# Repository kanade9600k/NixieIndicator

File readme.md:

# NixieIndicator

## 概要

* ニキシー管を制御するための基板
* 最大12管まで制御可能

## 回路図

## 外観

* 表

* 裏

## その他

* 高電圧注意
* 一応手元で動きましたが，動作保証はできません

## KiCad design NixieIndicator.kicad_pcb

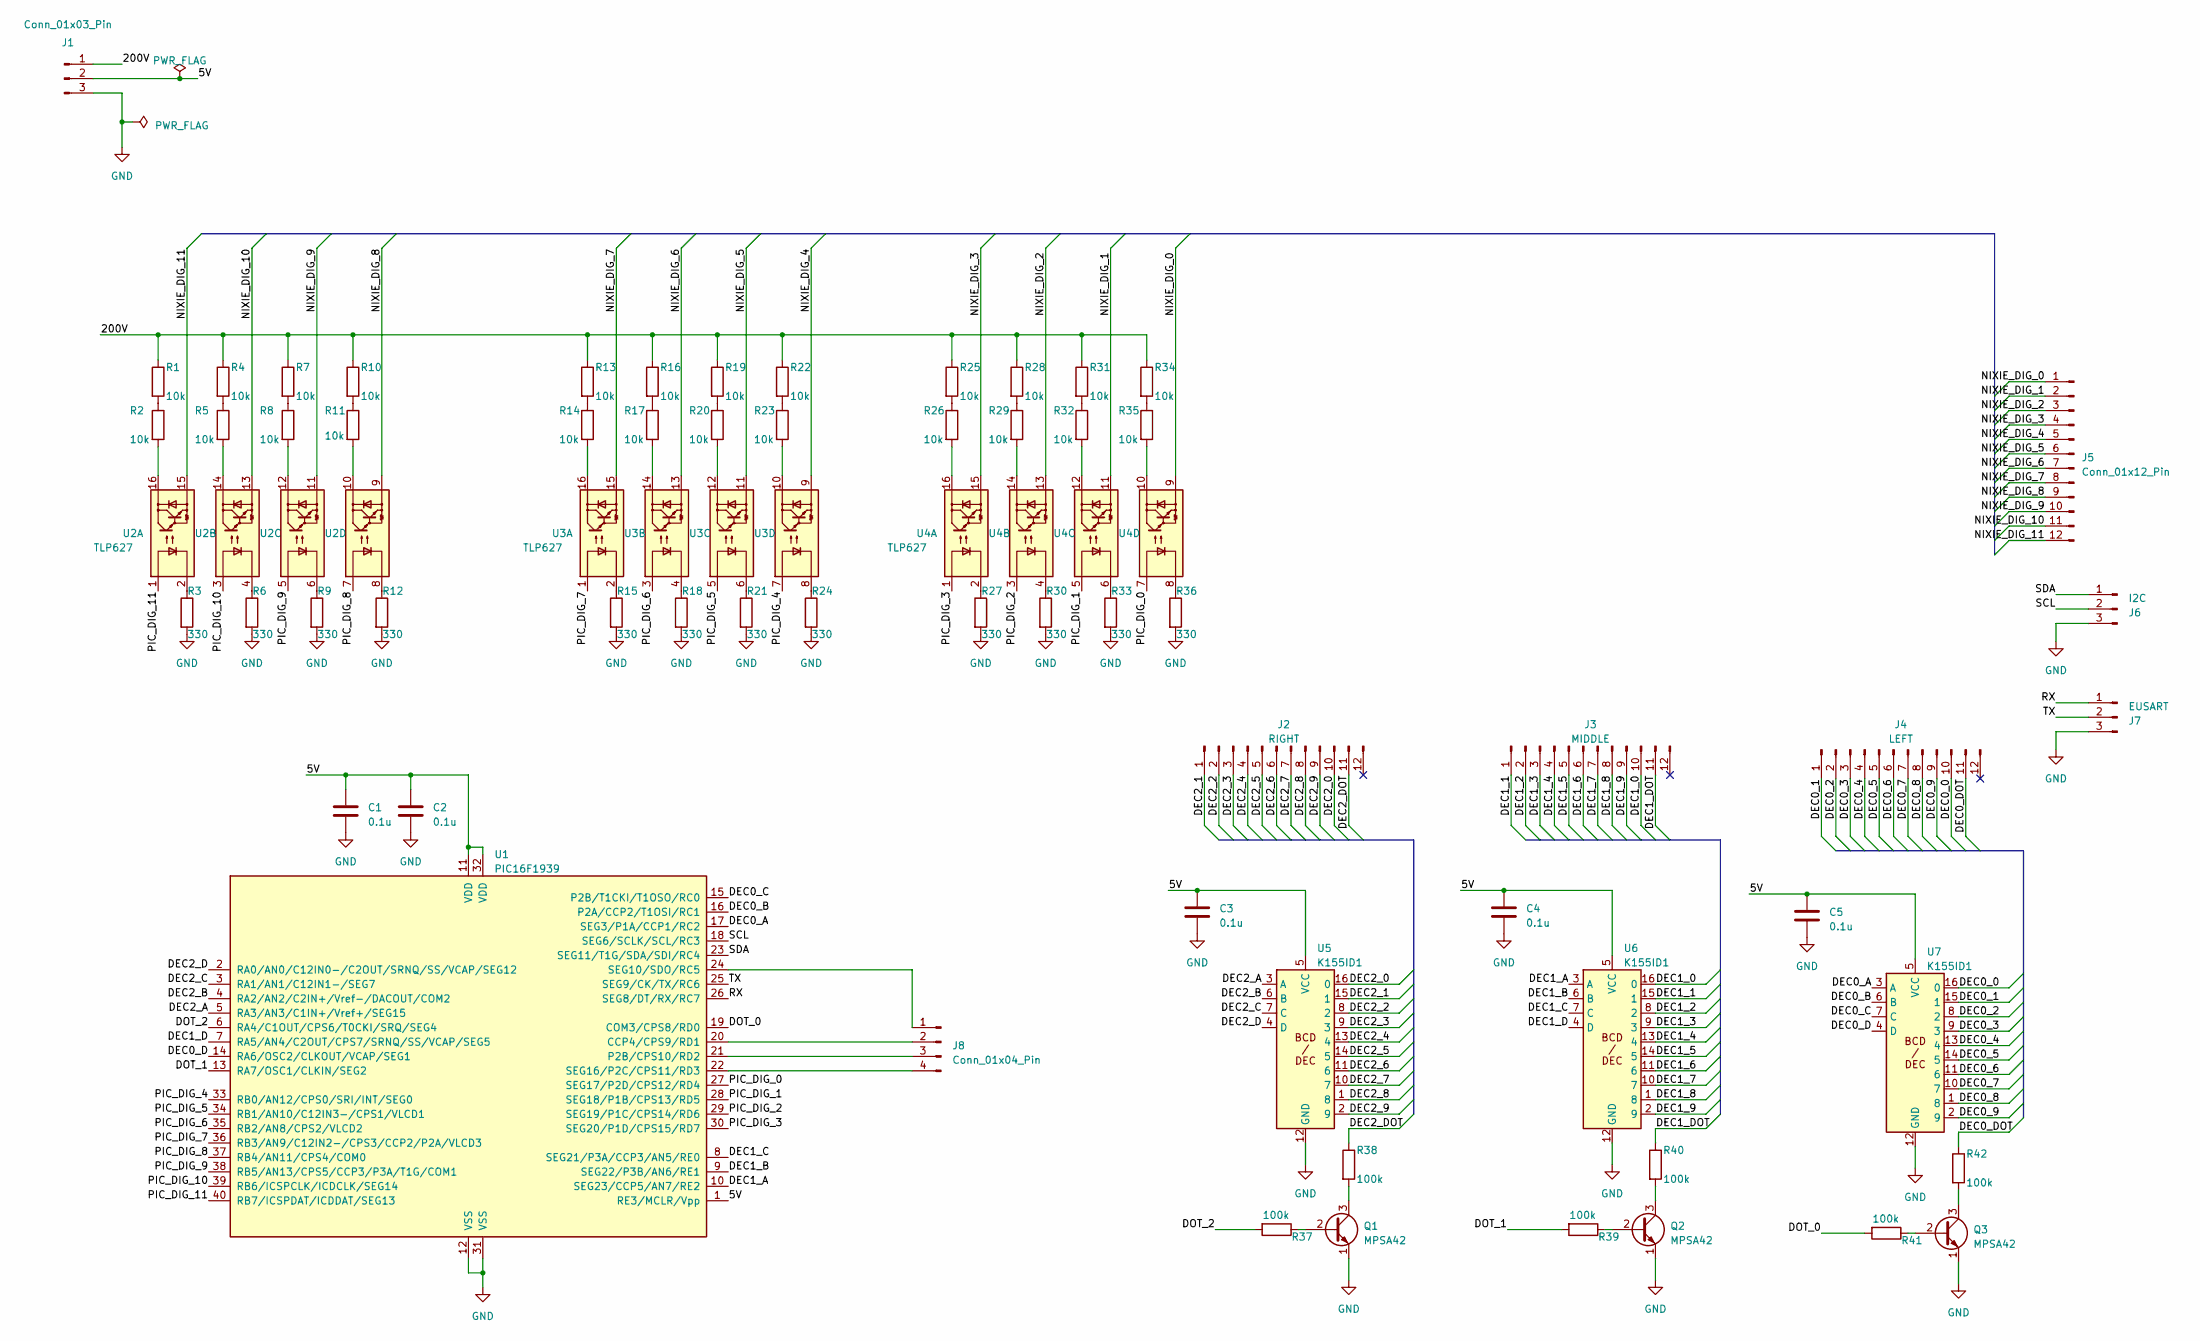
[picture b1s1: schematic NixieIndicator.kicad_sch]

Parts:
C1, C2, C3, C4, C5: 0.1u; C_Disc_D3.0mm_W2.0mm_P2.50mm
J1: Conn_01x03_Pin; JST_XH_B3B-XH-A_1x03_P2.50mm_Vertical
J2: RIGHT; JST_XH_S12B-XH-A_1x12_P2.50mm_Horizontal
J3: MIDDLE; JST_XH_S12B-XH-A_1x12_P2.50mm_Horizontal
J4: LEFT; JST_XH_S12B-XH-A_1x12_P2.50mm_Horizontal
J5: Conn_01x12_Pin; JST_XH_S12B-XH-A_1x12_P2.50mm_Horizontal
J6: I2C; JST_XH_B3B-XH-A_1x03_P2.50mm_Vertical
J7: EUSART; JST_XH_B3B-XH-A_1x03_P2.50mm_Vertical
J8: Conn_01x04_Pin; PinHeader_1x04_P2.54mm_Vertical
Q1, Q2, Q3: MPSA42; TO-92_Inline
R1, R2, R4, R5, R7, R8, R10, R11, R13, R14, R16, R17, R19, R20, R22, R23, R25, R26, R28, R29, R31, R32, R34, R35: 10k; R_Axial_DIN0207_L6.3mm_D2.5mm_P10.16mm_Horizontal
R3, R6, R9, R12, R15, R18, R21, R24, R27, R30, R33, R36: 330; R_Axial_DIN0207_L6.3mm_D2.5mm_P10.16mm_Horizontal
R37, R38, R39, R40, R41, R42: 100k; R_Axial_DIN0207_L6.3mm_D2.5mm_P10.16mm_Horizontal
U1: PIC16F1939; DIP-40_W15.24mm_Socket
U2, U3, U4: TLP627; DIP-16_W7.62mm_Socket
U5, U6, U7: K155ID1; DIP-16_W7.62mm_Socket

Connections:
/5V: C1.1, C2.1, C3.1, C4.1, C5.1, J1.2, U1.1 (RE3/MCLR/Vpp), U1.11 (VDD), U1.32 (VDD), U5.5 (VCC), U6.5 (VCC), U7.5 (VCC)
/200V: J1.1, R1.1, R4.1, R7.1, R10.1, R13.1, R16.1, R19.1, R22.1, R25.1, R28.1, R31.1, R34.1
/DEC0_0: J4.10, U7.16 (0)
/DEC0_1: J4.1, U7.15 (1)
/DEC0_2: J4.2, U7.8 (2)
/DEC0_3: J4.3, U7.9 (3)
/DEC0_4: J4.4, U7.13 (4)
/DEC0_5: J4.5, U7.14 (5)
/DEC0_6: J4.6, U7.11 (6)
/DEC0_7: J4.7, U7.10 (7)
/DEC0_8: J4.8, U7.1 (8)
/DEC0_9: J4.9, U7.2 (9)
/DEC0_A: U1.17 (SEG3/P1A/CCP1/RC2), U7.3 (A)
/DEC0_B: U1.16 (P2A/CCP2/T1OSI/RC1), U7.6 (B)
/DEC0_C: U1.15 (P2B/T1CKI/T1OSO/RC0), U7.7 (C)
/DEC0_D: U1.14 (RA6/OSC2/CLKOUT/VCAP/SEG1), U7.4 (D)
/DEC0_DOT: J4.11, R42.1
/DEC1_0: J3.10, U6.16 (0)
/DEC1_1: J3.1, U6.15 (1)
/DEC1_2: J3.2, U6.8 (2)
/DEC1_3: J3.3, U6.9 (3)
/DEC1_4: J3.4, U6.13 (4)
/DEC1_5: J3.5, U6.14 (5)
/DEC1_6: J3.6, U6.11 (6)
/DEC1_7: J3.7, U6.10 (7)
/DEC1_8: J3.8, U6.1 (8)
/DEC1_9: J3.9, U6.2 (9)
/DEC1_A: U1.10 (SEG23/CCP5/AN7/RE2), U6.3 (A)
/DEC1_B: U1.9 (SEG22/P3B/AN6/RE1), U6.6 (B)
/DEC1_C: U1.8 (SEG21/P3A/CCP3/AN5/RE0), U6.7 (C)
/DEC1_D: U1.7 (RA5/AN4/C2OUT/CPS7/SRNQ/SS/VCAP/SEG5), U6.4 (D)
/DEC1_DOT: J3.11, R40.1
/DEC2_0: J2.10, U5.16 (0)
/DEC2_1: J2.1, U5.15 (1)
/DEC2_2: J2.2, U5.8 (2)
/DEC2_3: J2.3, U5.9 (3)
/DEC2_4: J2.4, U5.13 (4)
/DEC2_5: J2.5, U5.14 (5)
/DEC2_6: J2.6, U5.11 (6)
/DEC2_7: J2.7, U5.10 (7)
/DEC2_8: J2.8, U5.1 (8)
/DEC2_9: J2.9, U5.2 (9)
/DEC2_A: U1.5 (RA3/AN3/C1IN+/Vref+/SEG15), U5.3 (A)
/DEC2_B: U1.4 (RA2/AN2/C2IN+/Vref-/DACOUT/COM2), U5.6 (B)
/DEC2_C: U1.3 (RA1/AN1/C12IN1-/SEG7), U5.7 (C)
/DEC2_D: U1.2 (RA0/AN0/C12IN0-/C2OUT/SRNQ/SS/VCAP/SEG12), U5.4 (D)
/DEC2_DOT: J2.11, R38.1
/DOT_0: R41.2, U1.19 (COM3/CPS8/RD0)
/DOT_1: R39.2, U1.13 (RA7/OSC1/CLKIN/SEG2)
/DOT_2: R37.2, U1.6 (RA4/C1OUT/CPS6/T0CKI/SRQ/SEG4)
/NIXIE_DIG_0: J5.1, U4.9
/NIXIE_DIG_1: J5.2, U4.11
/NIXIE_DIG_2: J5.3, U4.13
/NIXIE_DIG_3: J5.4, U4.15
/NIXIE_DIG_4: J5.5, U3.9
/NIXIE_DIG_5: J5.6, U3.11
/NIXIE_DIG_6: J5.7, U3.13
/NIXIE_DIG_7: J5.8, U3.15
/NIXIE_DIG_8: J5.9, U2.9
/NIXIE_DIG_9: J5.10, U2.11
/NIXIE_DIG_10: J5.11, U2.13
/NIXIE_DIG_11: J5.12, U2.15
/PIC_DIG_0: U1.27 (SEG17/P2D/CPS12/RD4), U4.7
/PIC_DIG_1: U1.28 (SEG18/P1B/CPS13/RD5), U4.5
/PIC_DIG_2: U1.29 (SEG19/P1C/CPS14/RD6), U4.3
/PIC_DIG_3: U1.30 (SEG20/P1D/CPS15/RD7), U4.1
/PIC_DIG_4: U1.33 (RB0/AN12/CPS0/SRI/INT/SEG0), U3.7
/PIC_DIG_5: U1.34 (RB1/AN10/C12IN3-/CPS1/VLCD1), U3.5
/PIC_DIG_6: U1.35 (RB2/AN8/CPS2/VLCD2), U3.3
/PIC_DIG_7: U1.36 (RB3/AN9/C12IN2-/CPS3/CCP2/P2A/VLCD3), U3.1
/PIC_DIG_8: U1.37 (RB4/AN11/CPS4/COM0), U2.7
/PIC_DIG_9: U1.38 (RB5/AN13/CPS5/CCP3/P3A/T1G/COM1), U2.5
/PIC_DIG_10: U1.39 (RB6/ICSPCLK/ICDCLK/SEG14), U2.3
/PIC_DIG_11: U1.40 (RB7/ICSPDAT/ICDDAT/SEG13), U2.1
/RX: J7.1, U1.26 (SEG8/DT/RX/RC7)
/SCL: J6.2, U1.18 (SEG6/SCLK/SCL/RC3)
/SDA: J6.1, U1.23 (SEG11/T1G/SDA/SDI/RC4)
/TX: J7.2, U1.25 (SEG9/CK/TX/RC6)
GND: C1.2, C2.2, C3.2, C4.2, C5.2, J1.3, J6.3, J7.3, Q1.1 (E), Q2.1 (E), Q3.1 (E), R3.2, R6.2, R9.2, R12.2, R15.2, R18.2, R21.2, R24.2, R27.2, R30.2, R33.2, R36.2, U1.12 (VSS), U1.31 (VSS), U5.12 (GND), U6.12 (GND), U7.12 (GND)
unnamed: J8.1, U1.24 (SEG10/SDO/RC5)
unnamed: J8.2, U1.20 (CCP4/CPS9/RD1)
unnamed: J8.3, U1.21 (P2B/CPS10/RD2)
unnamed: J8.4, U1.22 (SEG16/P2C/CPS11/RD3)
unnamed: Q1.2 (B), R37.1
unnamed: Q1.3 (C), R38.2
unnamed: Q2.2 (B), R39.1
unnamed: Q2.3 (C), R40.2
unnamed: Q3.2 (B), R41.1
unnamed: Q3.3 (C), R42.2
unnamed: R1.2, R2.1
unnamed: R2.2, U2.16
unnamed: R3.1, U2.2
unnamed: R4.2, R5.1
unnamed: R5.2, U2.14
unnamed: R6.1, U2.4
unnamed: R7.2, R8.1
unnamed: R8.2, U2.12
unnamed: R9.1, U2.6
unnamed: R10.2, R11.1
unnamed: R11.2, U2.10
unnamed: R12.1, U2.8
unnamed: R13.2, R14.1
unnamed: R14.2, U3.16
unnamed: R15.1, U3.2
unnamed: R16.2, R17.1
unnamed: R17.2, U3.14
unnamed: R18.1, U3.4
unnamed: R19.2, R20.1
unnamed: R20.2, U3.12
unnamed: R21.1, U3.6
unnamed: R22.2, R23.1
unnamed: R23.2, U3.10
unnamed: R24.1, U3.8
unnamed: R25.2, R26.1
unnamed: R26.2, U4.16
unnamed: R27.1, U4.2
unnamed: R28.2, R29.1
unnamed: R29.2, U4.14
unnamed: R30.1, U4.4
unnamed: R31.2, R32.1
unnamed: R32.2, U4.12
unnamed: R33.1, U4.6
unnamed: R34.2, R35.1
unnamed: R35.2, U4.10
unnamed: R36.1, U4.8

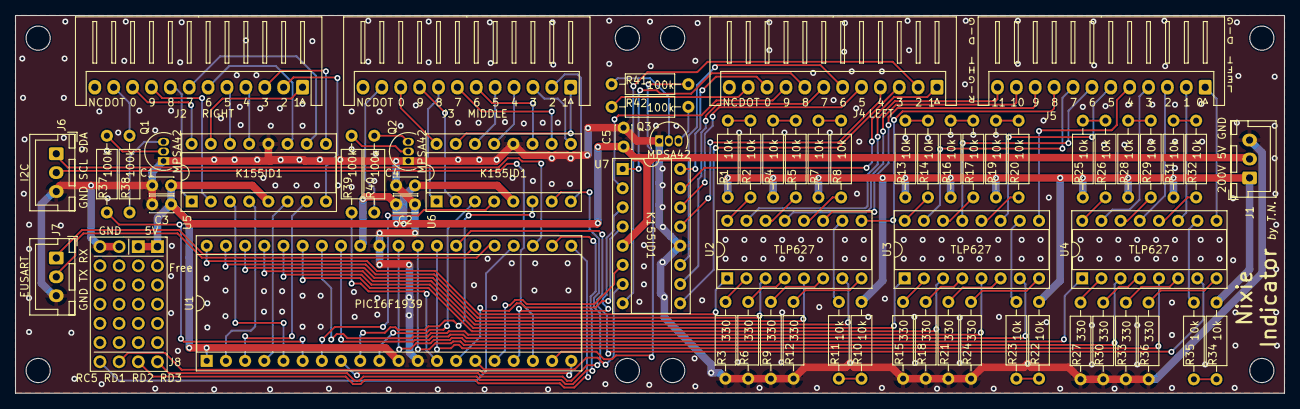
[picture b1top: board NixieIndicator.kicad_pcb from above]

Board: 2 copper layers, 168.0 x 50.0 mm, 65 parts (0 on the bottom side), 125 nets.

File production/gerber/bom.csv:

Designator,Footprint,Quantity,Value,LCSC Part #
"C1, C2, C3, C4, C5",C_Disc_D3.0mm_W2.0mm_P2.50mm,5,0.1u,
J1,JST_XH_B3B-XH-A_1x03_P2.50mm_Vertical,1,Conn_01x03_Pin,
J2,JST_XH_S12B-XH-A_1x12_P2.50mm_Horizontal,1,RIGHT,
J3,JST_XH_S12B-XH-A_1x12_P2.50mm_Horizontal,1,MIDDLE,
J4,JST_XH_S12B-XH-A_1x12_P2.50mm_Horizontal,1,LEFT,
J5,JST_XH_S12B-XH-A_1x12_P2.50mm_Horizontal,1,Conn_01x12_Pin,
J6,JST_XH_B3B-XH-A_1x03_P2.50mm_Vertical,1,I2C,
J7,JST_XH_B3B-XH-A_1x03_P2.50mm_Vertical,1,EUSART,
J8,PinHeader_1x04_P2.54mm_Vertical,1,Conn_01x04_Pin,
"Q1, Q2, Q3",TO-92_Inline,3,MPSA42,
"R1, R10, R11, R13, R14, R16, R17, R19, R2, R20, R22, R23, R25, R26, R28, R29, R31, R32, R34, R35, R4, R5, R7, R8",R_Axial_DIN0207_L6.3mm_D2.5mm_P10.16mm_Horizontal,24,10k,
"R12, R15, R18, R21, R24, R27, R3, R30, R33, R36, R6, R9",R_Axial_DIN0207_L6.3mm_D2.5mm_P10.16mm_Horizontal,12,330,
"R37, R38, R39, R40, R41, R42",R_Axial_DIN0207_L6.3mm_D2.5mm_P10.16mm_Horizontal,6,100k,
U1,DIP-40_W15.24mm_Socket,1,PIC16F1939,
"U2, U3, U4",DIP-16_W7.62mm_Socket,3,TLP627,
"U5, U6, U7",DIP-16_W7.62mm_Socket,3,K155ID1,

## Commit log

2023-03-21 最初のコミット
2023-05-27 製造後データを追加
2023-05-27 readmeを追加
